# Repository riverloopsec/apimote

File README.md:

apimote
=======

ApiMote IEEE 802.15.4/ZigBee Sniffing Hardware

The ApiMote v4beta version is beta hardware intended for researchers,
students, utility companies, etc. to use for learning about and 
evaluating the security of IEEE 802.15.4/ZigBee systems as authorized.

----

The design files are created in KiCad, and we reccomend opening them in
the latest version.

----
Copyright 2013-2014 River Loop Security, LLC
Released as Open-Source Hardware under the LICENSE.txt terms.
You *must* use this hardware (and any accompanying software) as authorized
by law, and it is provided pursuint to those terms. We *are not* responsible
for any unauthorized or illegal use of this research tool.

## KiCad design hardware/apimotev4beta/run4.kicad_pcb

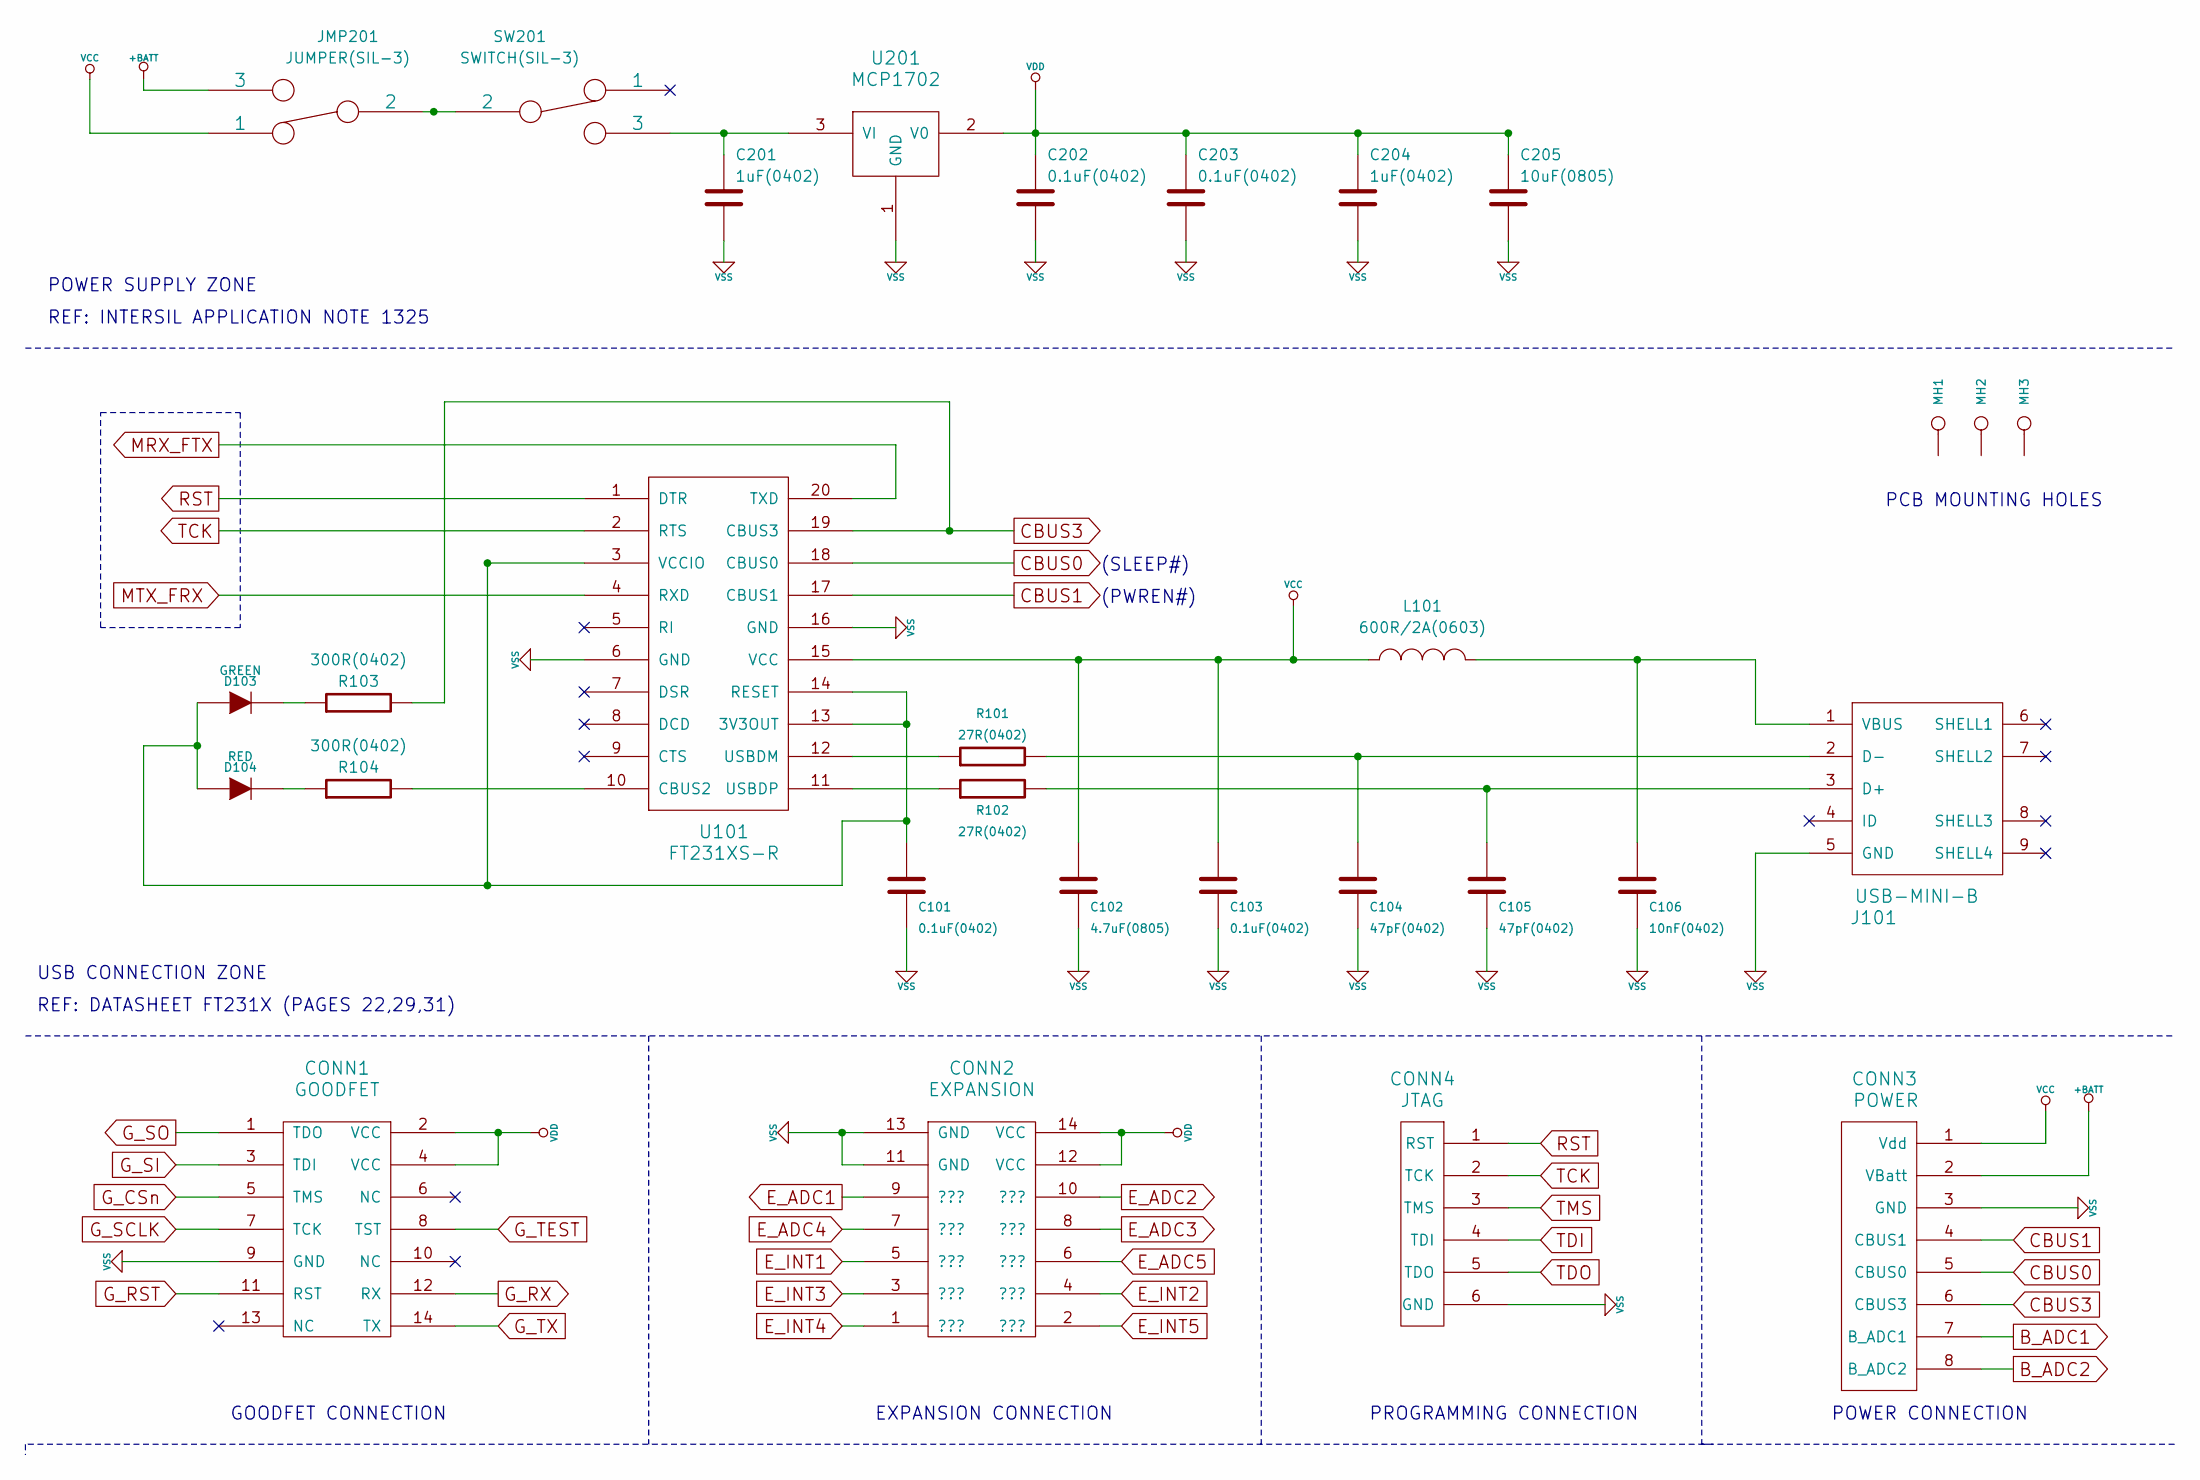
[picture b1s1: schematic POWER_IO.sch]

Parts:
C101, C103: 0.1uF(0402)
C102: 4.7uF(0805)
C104, C105: 47pF(0402)
C106: 10nF(0402)
C201, C204: 1uF(0402)
C202, C203: 0.1uF(0402)
C205: 10uF(0805)
CONN1: GOODFET
CONN2: EXPANSION
CONN3: POWER
CONN4: JTAG
D103: GREEN
D104: RED
J101: USB-MINI-B
JMP201: JUMPER(SIL-3)
L101: 600R/2A(0603)
MH1, MH2, MH3: Xmm
R101, R102: 27R(0402)
R103, R104: 300R(0402)
SW201: SWITCH(SIL-3)
U101: FT231XS-R
U201: MCP1702

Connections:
+BATT: CONN3.2 (VBatt), JMP201.3
B_ADC1: CONN3.7 (B_ADC1); also elsewhere on the board
B_ADC2: CONN3.8 (B_ADC2); also elsewhere on the board
CBUS0: CONN3.5 (CBUS0), U101.18 (CBUS0)
CBUS1: CONN3.4 (CBUS1), U101.17 (CBUS1)
CBUS3: CONN3.6 (CBUS3), R103.2, U101.19 (CBUS3)
E_ADC1: CONN2.9 (???); also elsewhere on the board
E_ADC2: CONN2.10 (???); also elsewhere on the board
E_ADC3: CONN2.8 (???); also elsewhere on the board
E_ADC4: CONN2.7 (???); also elsewhere on the board
E_ADC5: CONN2.6 (???); also elsewhere on the board
E_INT1: CONN2.5 (???); also elsewhere on the board
E_INT2: CONN2.4 (???); also elsewhere on the board
E_INT3: CONN2.3 (???); also elsewhere on the board
E_INT4: CONN2.1 (???); also elsewhere on the board
E_INT5: CONN2.2 (???); also elsewhere on the board
G_CSn: CONN1.5 (TMS); also elsewhere on the board
G_RST: CONN1.11 (RST); also elsewhere on the board
G_RX: CONN1.12 (RX); also elsewhere on the board
G_SCLK: CONN1.7 (TCK); also elsewhere on the board
G_SI: CONN1.3 (TDI); also elsewhere on the board
G_SO: CONN1.1 (TDO); also elsewhere on the board
G_TEST: CONN1.8 (TST); also elsewhere on the board
G_TX: CONN1.14 (TX); also elsewhere on the board
MRX_FTX: U101.20 (TXD); also elsewhere on the board
MTX_FRX: U101.4 (RXD); also elsewhere on the board
unnamed: C105.1, J101.3 (D+), R102.2
unnamed: C104.1, J101.2 (D-), R101.2
unnamed: JMP201.2, SW201.2
unnamed: R104.2, U101.10 (CBUS2)
unnamed: C101.1, D103.1 (A), D104.1 (A), U101.3 (VCCIO), U101.13 (3V3OUT), U101.14 (RESET)
unnamed: R102.1, U101.11 (USBDP)
unnamed: R101.1, U101.12 (USBDM)
unnamed: C106.1, J101.1 (VBUS), L101.2
unnamed: D103.2 (K), R103.1
unnamed: D104.2 (K), R104.1
unnamed 54: C201.1, SW201.3, U201.3 (VI); also elsewhere on the board
RST: CONN4.1 (RST), U101.1 (DTR); also elsewhere on the board
TCK: CONN4.2 (TCK), U101.2 (RTS); also elsewhere on the board
TDI: CONN4.4 (TDI); also elsewhere on the board
TDO: CONN4.5 (TDO); also elsewhere on the board
TMS: CONN4.3 (TMS); also elsewhere on the board
VCC: C102.1, C103.1, CONN3.1 (Vdd), JMP201.1, L101.1, U101.15 (VCC)
VDD: C202.1, C203.1, C204.1, C205.1, CONN1.2 (VCC), CONN1.4 (VCC), CONN2.12 (VCC), CONN2.14 (VCC), U201.2 (V0); also elsewhere on the board
VSS: C101.2, C102.2, C103.2, C104.2, C105.2, C106.2, C201.2, C202.2, C203.2, C204.2, C205.2, CONN1.9 (GND), CONN2.11 (GND), CONN2.13 (GND), CONN3.3 (GND), CONN4.6 (GND), J101.5 (GND), U101.6 (GND), U101.16 (GND), U201.1 (GND); also elsewhere on the board

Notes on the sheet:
POWER SUPPLY ZONE
USB CONNECTION ZONE
GOODFET CONNECTION
EXPANSION CONNECTION
PROGRAMMING CONNECTION
POWER CONNECTION
(SLEEP#)
(PWREN#)
REF: INTERSIL APPLICATION NOTE 1325
REF: DATASHEET FT231X (PAGES 22,29,31)
PCB MOUNTING HOLES

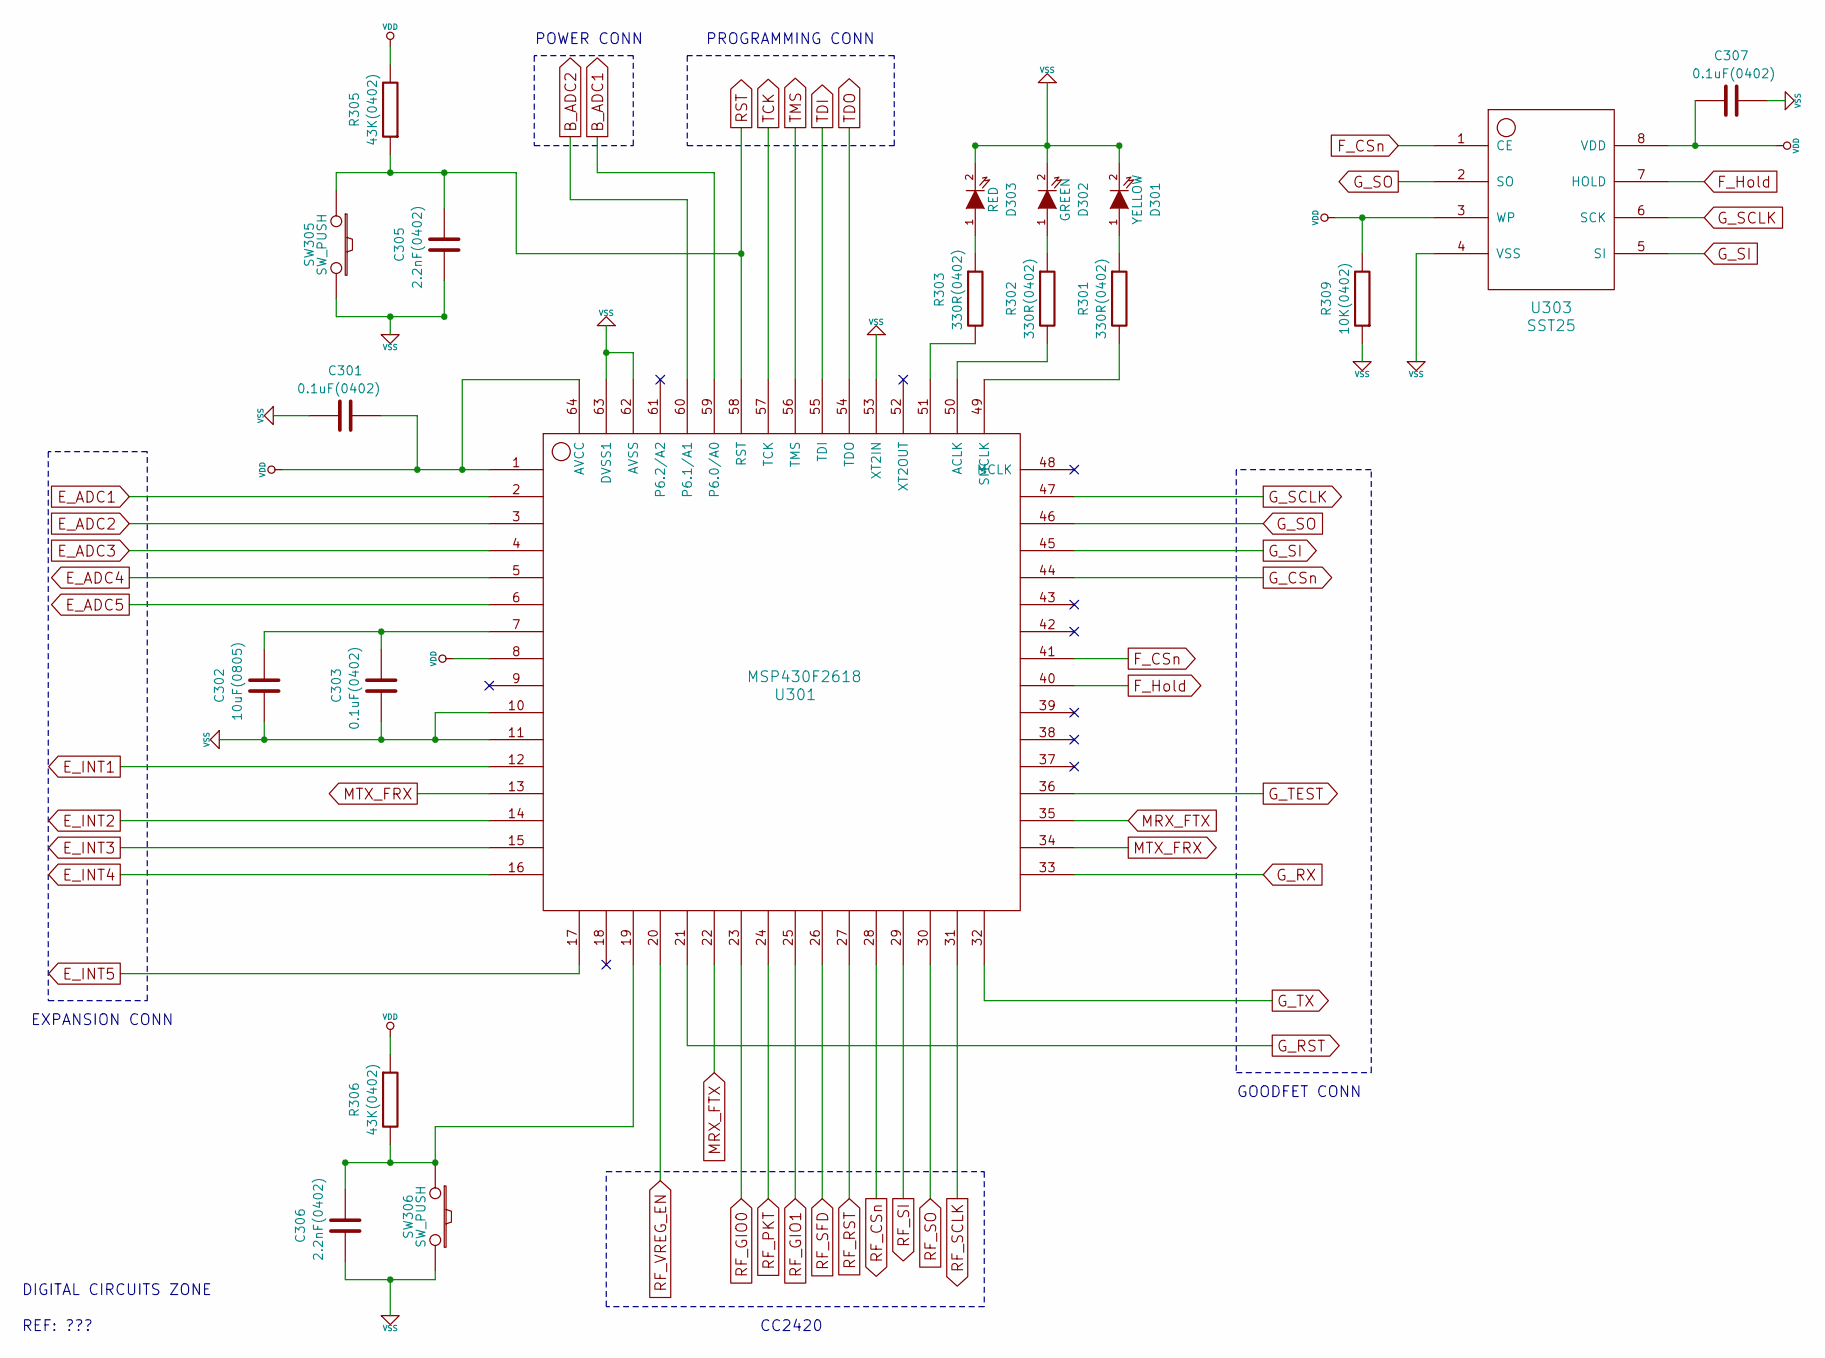
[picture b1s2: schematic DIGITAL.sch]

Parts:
C301, C303, C307: 0.1uF(0402)
C302: 10uF(0805)
C305, C306: 2.2nF(0402)
D301: YELLOW
D302: GREEN
D303: RED
R301, R302, R303: 330R(0402)
R305, R306: 43K(0402)
R309: 10K(0402)
SW305, SW306: SW_PUSH
U301: MSP430F2618
U303: SST25

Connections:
B_ADC1: U301.59 (P6.0/A0); also elsewhere on the board
B_ADC2: U301.60 (P6.1/A1); also elsewhere on the board
E_ADC1: U301.2; also elsewhere on the board
E_ADC2: U301.3; also elsewhere on the board
E_ADC3: U301.4; also elsewhere on the board
E_ADC4: U301.5; also elsewhere on the board
E_ADC5: U301.6; also elsewhere on the board
E_INT1: U301.12; also elsewhere on the board
E_INT2: U301.14; also elsewhere on the board
E_INT3: U301.15; also elsewhere on the board
E_INT4: U301.16; also elsewhere on the board
E_INT5: U301.17; also elsewhere on the board
F_CSn: U301.41, U303.1 (CE)
F_Hold: U301.40, U303.7 (HOLD)
G_CSn: U301.44; also elsewhere on the board
G_RST: U301.21; also elsewhere on the board
G_RX: U301.33; also elsewhere on the board
G_SCLK: U301.47, U303.6 (SCK); also elsewhere on the board
G_SI: U301.45, U303.5 (SI); also elsewhere on the board
G_SO: U301.46, U303.2 (SO); also elsewhere on the board
G_TEST: U301.36; also elsewhere on the board
G_TX: U301.32; also elsewhere on the board
MRX_FTX: U301.22, U301.35; also elsewhere on the board
MTX_FRX: U301.13, U301.34; also elsewhere on the board
unnamed: C302.1, C303.1, U301.7
unnamed: R301.2, U301.49 (SMCLK)
unnamed: R303.2, U301.51
unnamed: R302.2, U301.50 (ACLK)
unnamed: D303.1 (A), R303.1
unnamed: D302.1 (A), R302.1
unnamed: D301.1 (A), R301.1
unnamed: C306.1, R306.2, SW306.1, U301.19
RF_CSn: U301.28; also elsewhere on the board
RF_GIO0: U301.23; also elsewhere on the board
RF_GIO1: U301.25; also elsewhere on the board
RF_PKT: U301.24; also elsewhere on the board
RF_RST: U301.27; also elsewhere on the board
RF_SCLK: U301.31; also elsewhere on the board
RF_SFD: U301.26; also elsewhere on the board
RF_SI: U301.29; also elsewhere on the board
RF_SO: U301.30; also elsewhere on the board
RF_VREG_EN: U301.20; also elsewhere on the board
RST: C305.1, R305.1, SW305.1, U301.58 (RST); also elsewhere on the board
TCK: U301.57 (TCK); also elsewhere on the board
TDI: U301.55 (TDI); also elsewhere on the board
TDO: U301.54 (TDO); also elsewhere on the board
TMS: U301.56 (TMS); also elsewhere on the board
VDD: C301.2, C307.1, R305.2, R306.1, R309.2, U301.1, U301.8, U301.64 (AVCC), U303.3 (WP), U303.8 (VDD); also elsewhere on the board
VSS: C301.1, C302.2, C303.2, C305.2, C306.2, C307.2, D301.2 (K), D302.2 (K), D303.2 (K), R309.1, SW305.2, SW306.2, U301.10, U301.11, U301.53 (XT2IN), U301.62 (AVSS), U301.63 (DVSS1), U303.4 (VSS); also elsewhere on the board

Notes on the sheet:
DIGITAL CIRCUITS ZONE
CC2420
GOODFET CONN
EXPANSION CONN
PROGRAMMING CONN
POWER CONN
REF: ???

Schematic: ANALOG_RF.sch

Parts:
ANT1: RP-SMA
ANT2: INVERTED_F
C401, C404, C405, C406, C413: 0.1uF(0402)
C402: 10nF(0402)
C403, C407, C408, C414: 68pF(0402)
C410, C412: 10uF(0805)
C450, C451: 27pF(0402)
C501, C702: 5.6pF(0402)
C701, C703: 0.5pF(0402)
L401: 60(0603)
L701, L703: 7.5nH(0402)
L702: 5.6nH(0402)
R401, R405, R406: 43K(0402)
R402: 2R(0603)
U401: CC2420
Y450: 16MHZ(2010)

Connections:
+1.8V: C401.2, C402.2, C403.2, C405.1, C406.1, C407.1, C408.2, C414.2, R402.1, U401.1 (VCO_GRD), U401.2 (AVDD_VCO), U401.3 (AVDD_PRE), U401.4 (AVDD_RF1), U401.10 (AVDD_SW), U401.14 (AVDD_RF2), U401.15 (AVDD_IF2), U401.17 (AVDD_ADC), U401.18 (DVDD_ADC), U401.20 (DGRD), U401.26 (DVDD1.8), U401.35 (DVDD_RAM), U401.37 (AVDD_XOSC16), U401.42 (VREG_OUT), U401.44 (AVDD_IF1), U401.48 (AVDD_CHP)
+3.3V: C404.1, C412.1, L401.2, R406.1, U401.25 (DVDD3.3), U401.43 (VREG_IN)
/ANALOG_RF/RF_EXT_ANT: ANT1.5 (RF), C501.3
unnamed: C410.1, R402.2
unnamed: C501.2, C703.1, L701.1
unnamed: C701.1, L701.2, L703.1, U401.8 (RF_N)
unnamed: R401.2, U401.45 (R_BIAS)
unnamed: C703.2, L702.2, L703.2, U401.6 (RF_P)
unnamed: C702.2, L702.1, U401.7 (TXRX_SW)
unnamed: C451.2, U401.39 (XOSC116_Q1), Y450.1
unnamed: C450.2, U401.38 (XOSC16_Q2), Y450.2
RF_CSn: U401.31 (CSn); also elsewhere on the board
RF_GIO0: U401.30 (FIFO); also elsewhere on the board
RF_GIO1: U401.28 (CCA); also elsewhere on the board
RF_PKT: U401.29 (FIFOP); also elsewhere on the board
RF_RST: R406.2, U401.21 (RESETn); also elsewhere on the board
RF_SCLK: U401.32 (SCLK); also elsewhere on the board
RF_SFD: U401.27 (SFD); also elsewhere on the board
RF_SI: U401.33 (SI); also elsewhere on the board
RF_SO: U401.34 (SO); also elsewhere on the board
RF_VREG_EN: R405.2, U401.41 (VREG_EN); also elsewhere on the board
VDD: C413.1, L401.1; also elsewhere on the board
VSS: ANT1.1 (GND), ANT1.2 (GND), ANT1.3 (GND), ANT1.4 (GND), ANT2.1 (RF), ANT2.2 (GND), C401.1, C402.1, C403.1, C404.2, C405.2, C406.2, C407.2, C408.1, C410.2, C412.2, C413.2, C414.1, C450.1, C451.1, C501.1, C701.2, C702.1, R401.1, R405.1, U401.5 (GND), U401.9 (GND), U401.19 (DGND_GRD), U401.22 (DNGD), U401.23 (DSUB_PADS), U401.24 (DSUB_CORE), U401.49 (GND_EX); also elsewhere on the board

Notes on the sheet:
RF ZONE
MSP430 (SHEET2)
REF: TI DESIGN REFERENCE CC2420DB - PAGE 2 (SCHEMATIC RF SECTION)

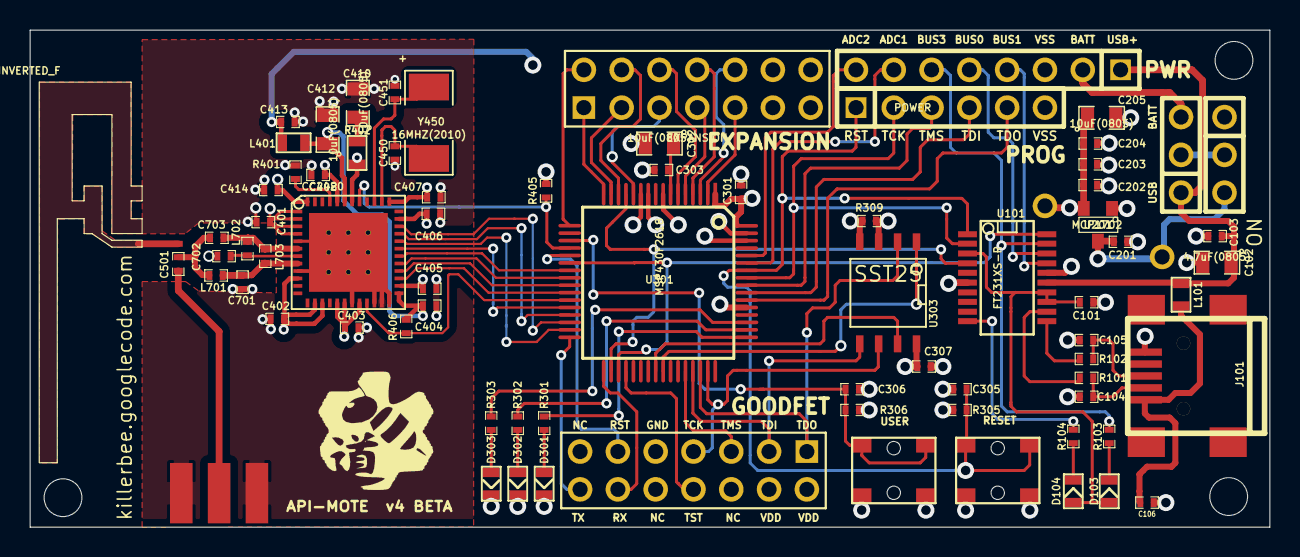
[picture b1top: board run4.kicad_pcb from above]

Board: 4 copper layers, 83.3 x 33.4 mm, 83 parts (0 on the bottom side), 76 nets.

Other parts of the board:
PIN_ARRAY_1, PIN_ARRAY_1#2, PIN_ARRAY_1#3, PIN_ARRAY_1#4: Val**; TAP

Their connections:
unnamed 54: PIN_ARRAY_1#3.1; also elsewhere on the board
VDD: PIN_ARRAY_1#4.1; also elsewhere on the board

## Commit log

2014-03-18 license file added, readme updated
2014-03-18 apimote v4beta files added
2014-03-18 added pdf infosheet
2014-03-20 add image of v4beta to readme page
2014-03-20 updage img
2014-06-01 adding the apimote v4beta BOM
